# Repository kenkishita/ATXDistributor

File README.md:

# ATXDistributor
This is an ATX power distributor board inspired and based on https://github.com/geniekobayashi/bitfab/tree/master/atx_psu_distributer. 

#Specifications:

PCB seize 73.66mm x 45.25mm  
24Pin right angle ATX connector  
12V right angle screw terminal block (++ —-)   
5V right angle screw terminal block  
3.3V right angle screw terminal block  
12V for FAN connector (JSR B2B-XH-A)  
5Vsb for RaspberryPi connector (JSR B2B-XH-A)  
PS_ON connector (JSR B2B-XH-A)  
PWR_OK LED (Discrete LED or 0604 type SMD LED)  
20Ω/5W cement resistor (R1)  
220Ω/1W carbon resistor (R2)  
1kohm LED resistor (R3 or R4)  

# License
CC BY-NC 3.0  
http://creativecommons.org/licenses/by-nc/3.0/

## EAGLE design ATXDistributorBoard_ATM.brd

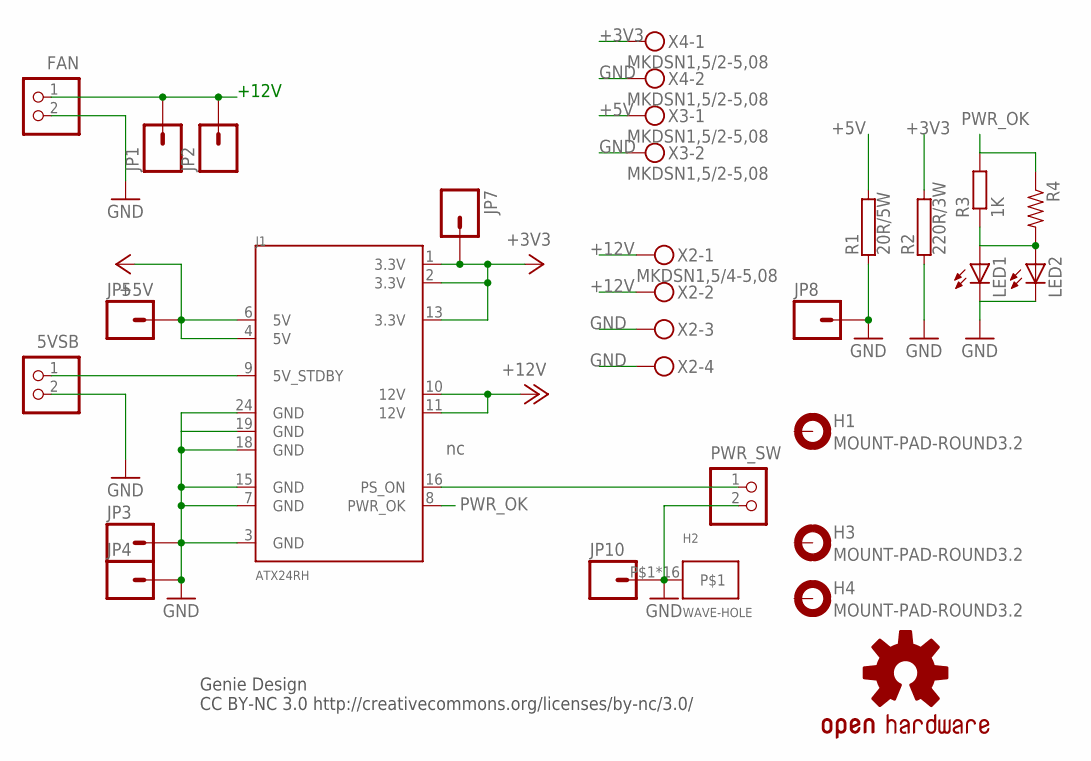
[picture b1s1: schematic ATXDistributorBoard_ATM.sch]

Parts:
5VSB: B2B-XH-A
FAN: B2B-XH-A
H1, H3, H4: MOUNT-PAD-ROUND3.2; 3,2-PAD
H2: WAVE-HOLE; 3,0-WAVE-HOLE
J1: ATX24RH; ATX24_RIGHT_ANGLE
JP1, JP2, JP3, JP4, JP5, JP7, JP8, JP10: M01PTH_NO_SILK_YES_STOP; 1X01_NO_SILK
LED1: LED3MM
LED2: LED_ESML0603; LED_SML0603
LOGO1: OSHW-LOGOS-COPPER; OSHW-LOGO-S_COPPER
PWR_SW: B2B-XH-A
R1: 20R/5W; HPS923
R2: 220R/3W; CA4050
R3: 1K; 0207/10
R4: RESISTOR0603-RES; 0603-RES
X2: MKDSN1,5/4-5,08
X3, X4: MKDSN1,5/2-5,08

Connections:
5VSB: 5VSB.1, J1.9 (5V_STDBY)
+3V3: J1.1 (3.3V), J1.2 (3.3V), J1.13 (3.3V), JP7.1, R2.2, X4.1
+5V: J1.4 (5V), J1.6 (5V), JP5.1, R1.2, X3.1
+12V: FAN.1, J1.10 (12V), J1.11 (12V), JP1.1, JP2.1, X2.1, X2.2
GND: 5VSB.2, FAN.2, H2.P$1, H2.P$2, H2.P$3, H2.P$4, H2.P$5, H2.P$6, H2.P$7, H2.P$8, H2.P$17, H2.P$18, H2.P$19, H2.P$20, H2.P$21, H2.P$22, H2.P$23, H2.P$24, J1.3 (GND), J1.7 (GND), J1.15 (GND), J1.18 (GND), J1.19 (GND), J1.24 (GND), JP3.1, JP4.1, JP8.1, JP10.1, LED1.K (C), LED2.C, PWR_SW.2, R1.1, R2.1, X2.3, X2.4, X3.2, X4.2
unnamed: LED1.A, LED2.A, R3.1, R4.2
PS_ON: J1.16 (PS_ON), PWR_SW.1
PWR_OK: J1.8 (PWR_OK), R3.2, R4.1

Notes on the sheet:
Genie Design CC BY-NC 3.0 http://creativecommons.org/licenses/by-nc/3.0/
+12V

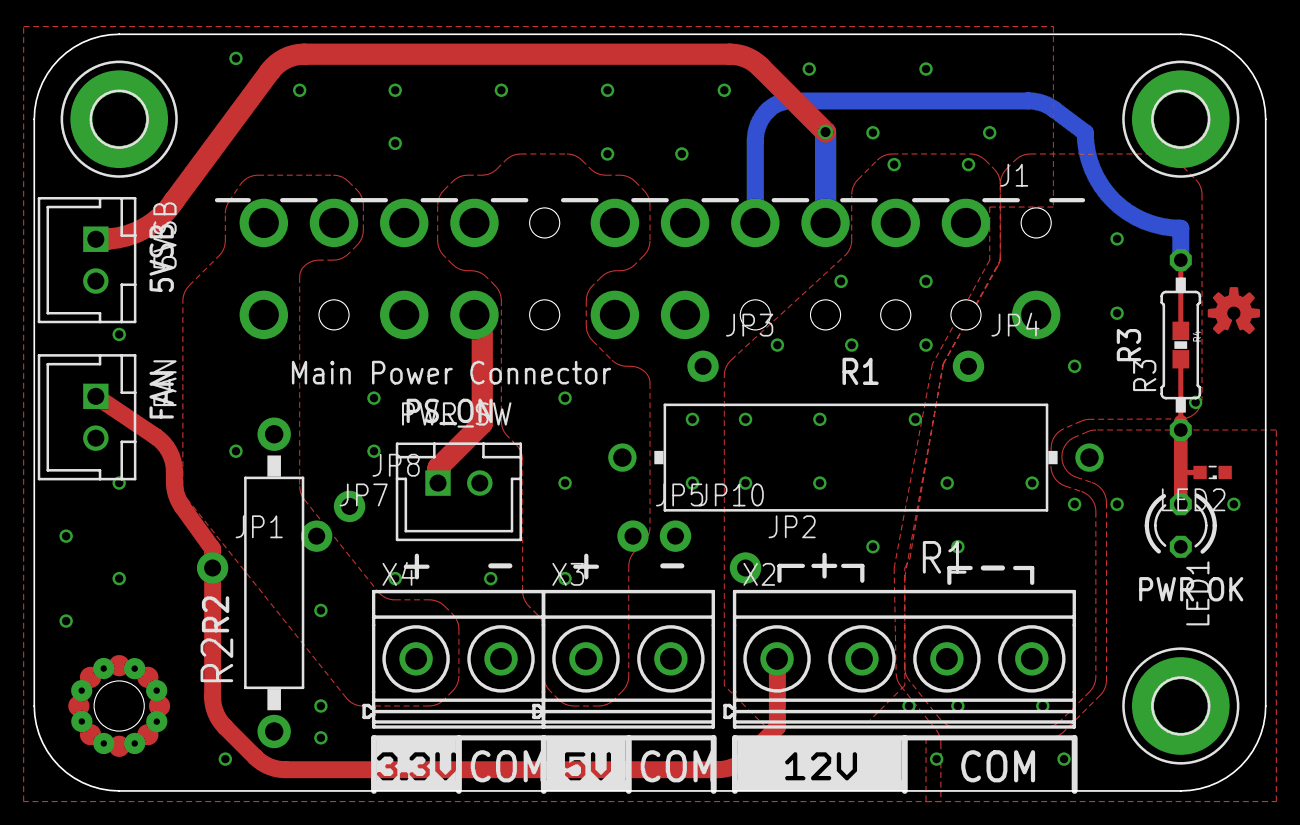
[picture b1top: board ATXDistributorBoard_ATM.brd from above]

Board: 2 copper layers, 73.7 x 45.3 mm, 26 parts (0 on the bottom side), 8 nets.

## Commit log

2016-05-14 initial
2016-05-21 add PCB board image

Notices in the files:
parts and their libraries:
SparkFun-Connectors: Licensing: Creative Commons ShareAlike 4.0 International - https://creativecommons.org/licenses/by-sa/4.0
SparkFun: Licensing: CC v3.0 Share-Alike You are welcome to use this library for commercial purposes.
